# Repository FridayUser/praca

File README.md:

View this project on [CADLAB.io](https://cadlab.io/project/28597). 

# praca

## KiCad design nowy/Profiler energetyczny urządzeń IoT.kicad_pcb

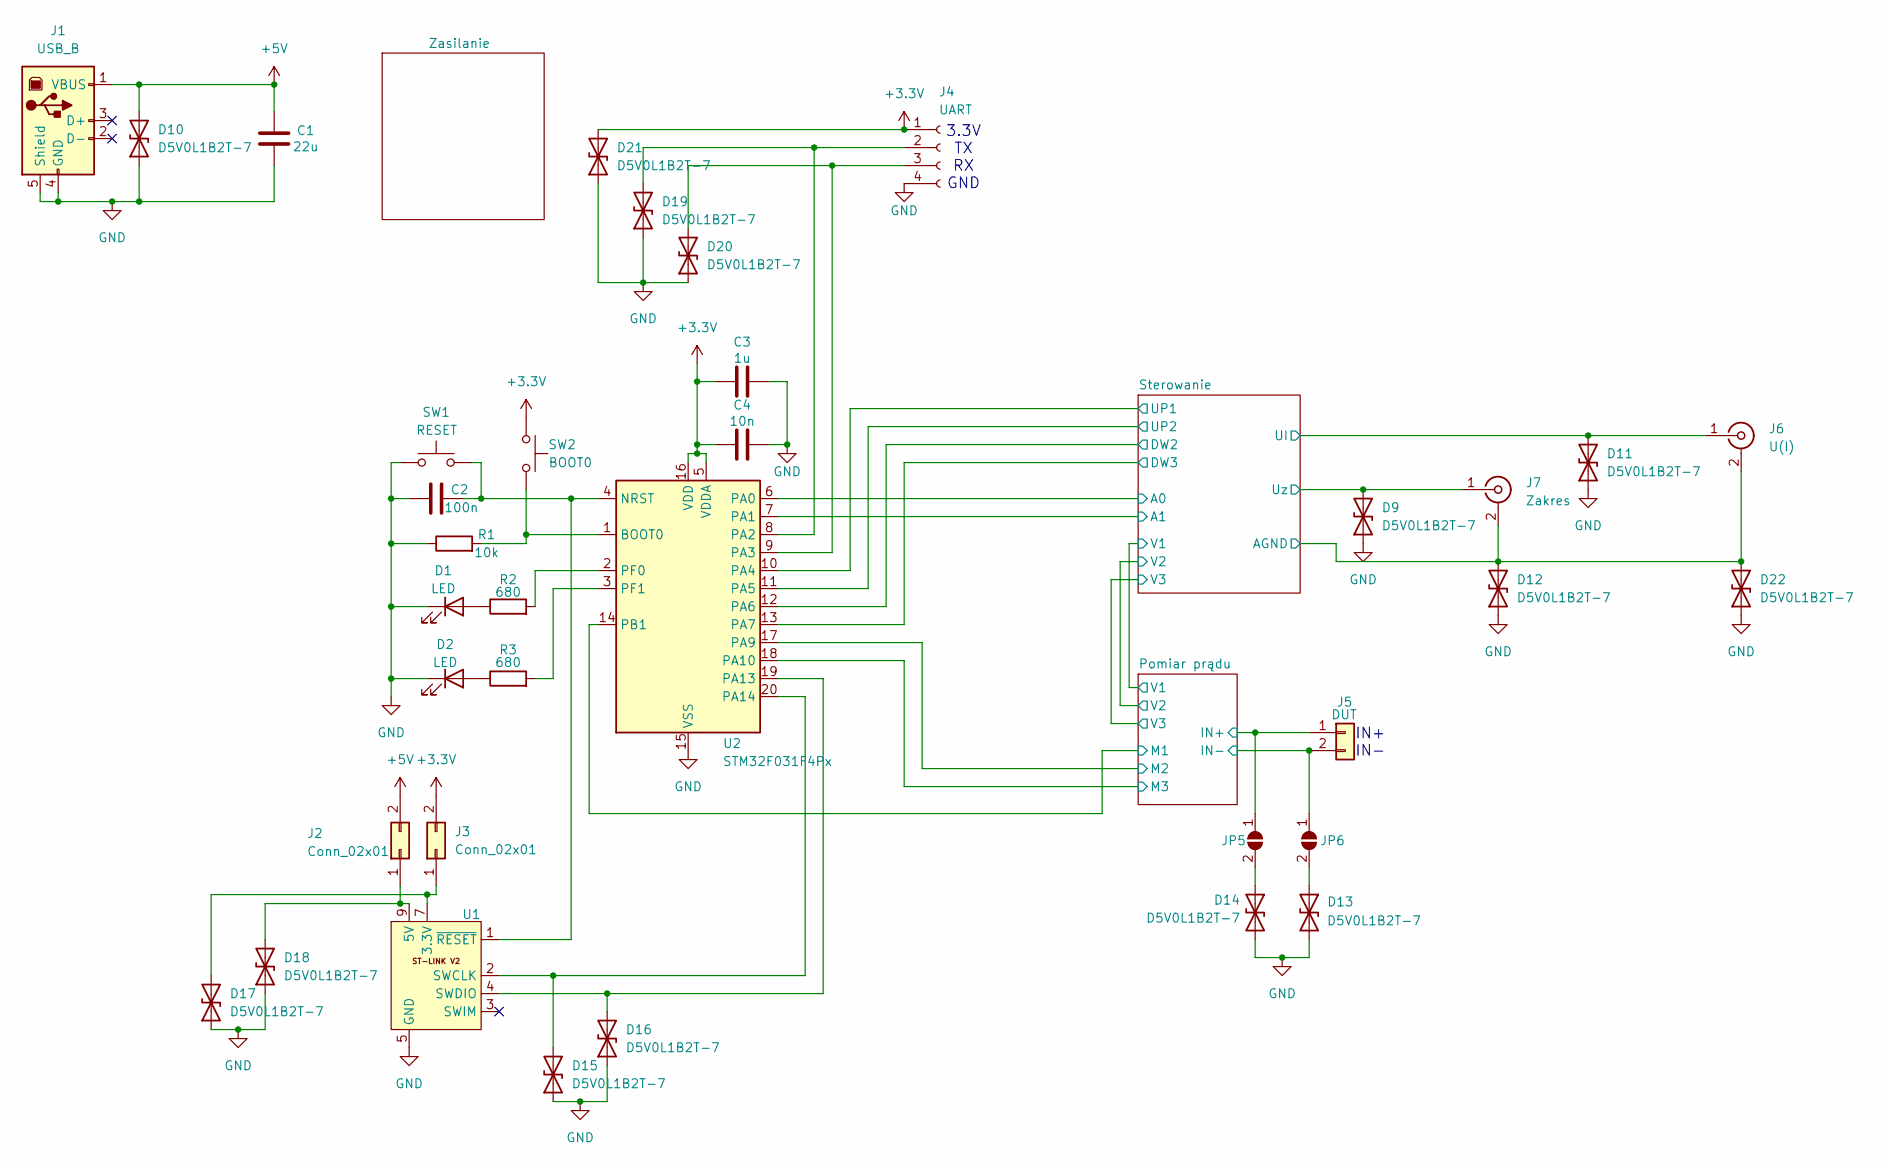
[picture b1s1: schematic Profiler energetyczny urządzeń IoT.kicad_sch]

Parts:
C1: 22u; C_1206_3216Metric_Pad1.33x1.80mm_HandSolder
C2: 100n; C_0805_2012Metric_Pad1.18x1.45mm_HandSolder
C3: 1u; C_0805_2012Metric_Pad1.18x1.45mm_HandSolder
C4: 10n; C_0805_2012Metric_Pad1.18x1.45mm_HandSolder
D1, D2: LED; LED_miniPLCC_2315_Handsoldering
D9, D10, D11, D12, D13, D14, D15, D16, D17, D18, D19, D20, D21, D22: D5V0L1B2T-7; D_SOD-523
J1: USB_B; USB_B_OST_USB-B1HSxx_Horizontal
J2, J3: Conn_02x01; PinHeader_2x01_P2.54mm_Vertical
J4: UART; PinSocket_1x04_P2.54mm_Vertical
J5: DUT; SolderWire-2sqmm_1x02_P7.8mm_D2mm_OD3.9mm
J6: U(I); BNC_Amphenol_B6252HB-NPP3G-50_Horizontal
J7: Zakres; BNC_Amphenol_B6252HB-NPP3G-50_Horizontal
JP5, JP6: SolderJumper_2_Open; SolderJumper-2_P1.3mm_Open_TrianglePad1.0x1.5mm
R1: 10k; R_0805_2012Metric_Pad1.20x1.40mm_HandSolder
R2, R3: 680; R_0805_2012Metric_Pad1.20x1.40mm_HandSolder
SW1: RESET; SW_SPST_TL3305A
SW2: BOOT0; SW_SPST_TL3305A
U1: IDC-Header_2x05_P2.54mm_Vertical
U2: STM32F031F4Px; TSSOP-20_4.4x6.5mm_P0.65mm

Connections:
3.3V: D17.2 (A2), J3.1, U1.7 (3.3V), U1.8 (3.3V)
5V: D18.2 (A2), J2.1, U1.9 (5V), U1.10 (5V)
+3.3V: C3.1, C4.1, D21.2 (A2), J3.2, J4.1, SW2.1, U2.5 (VDDA), U2.16 (VDD); also elsewhere on the board
+5V: C1.1, D10.2 (A2), J1.1 (VBUS), J2.2; also elsewhere on the board
/M3: U2.18 (PA10)
/Pomiar prądu/IN+: J5.1, JP5.1 (A); also elsewhere on the board
/Pomiar prądu/M1: U2.14 (PB1); also elsewhere on the board
/Pomiar prądu/M2: U2.17 (PA9); also elsewhere on the board
/Sterowanie/A0: U2.6 (PA0); also elsewhere on the board
/Sterowanie/A1: U2.7 (PA1); also elsewhere on the board
/Sterowanie/DW2: U2.12 (PA6); also elsewhere on the board
/Sterowanie/DW3: U2.13 (PA7); also elsewhere on the board
/Sterowanie/UI: D11.2 (A2), J6.1 (In); also elsewhere on the board
/Sterowanie/UP1: U2.10 (PA4); also elsewhere on the board
/Sterowanie/UP2: U2.11 (PA5); also elsewhere on the board
/Sterowanie/Uz: D9.2 (A2), J7.1 (In); also elsewhere on the board
GND: C1.2, C2.1, C3.2, C4.2, D1.1 (K), D2.1 (K), D9.1 (A1), D10.1 (A1), D11.1 (A1), D12.1 (A1), D12.2 (A2), D13.2 (A2), D14.2 (A2), D15.1 (A1), D16.1 (A1), D17.1 (A1), D18.1 (A1), D19.1 (A1), D20.1 (A1), D21.1 (A1), D22.1 (A1), D22.2 (A2), J1.4 (GND), J1.5 (Shield), J4.4, J5.2, J6.2 (Ext), J7.2 (Ext), JP6.1 (A), R1.1, SW1.1, U1.5 (GND), U1.6 (GND), U2.15 (VSS); also elsewhere on the board
unnamed: D1.2 (A), R2.1
unnamed: D2.2 (A), R3.1
unnamed: D13.1 (A1), JP6.2 (B)
unnamed: D14.1 (A1), JP5.2 (B)
unnamed: D15.2 (A2), U1.2 (SWCLK), U2.20 (PA14)
unnamed: D16.2 (A2), U1.4 (SWDIO), U2.19 (PA13)
unnamed: D19.2 (A2), J4.2, U2.8 (PA2)
unnamed: D20.2 (A2), J4.3, U2.9 (PA3)
unnamed: C2.2, SW1.2, U1.1 (~RESET), U2.4 (NRST)
unnamed: R1.2, SW2.2, U2.1 (BOOT0)
unnamed: R2.2, U2.2 (PF0)
unnamed: R3.2, U2.3 (PF1)

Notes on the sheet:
IN+ IN-
3.3V TX RX GND

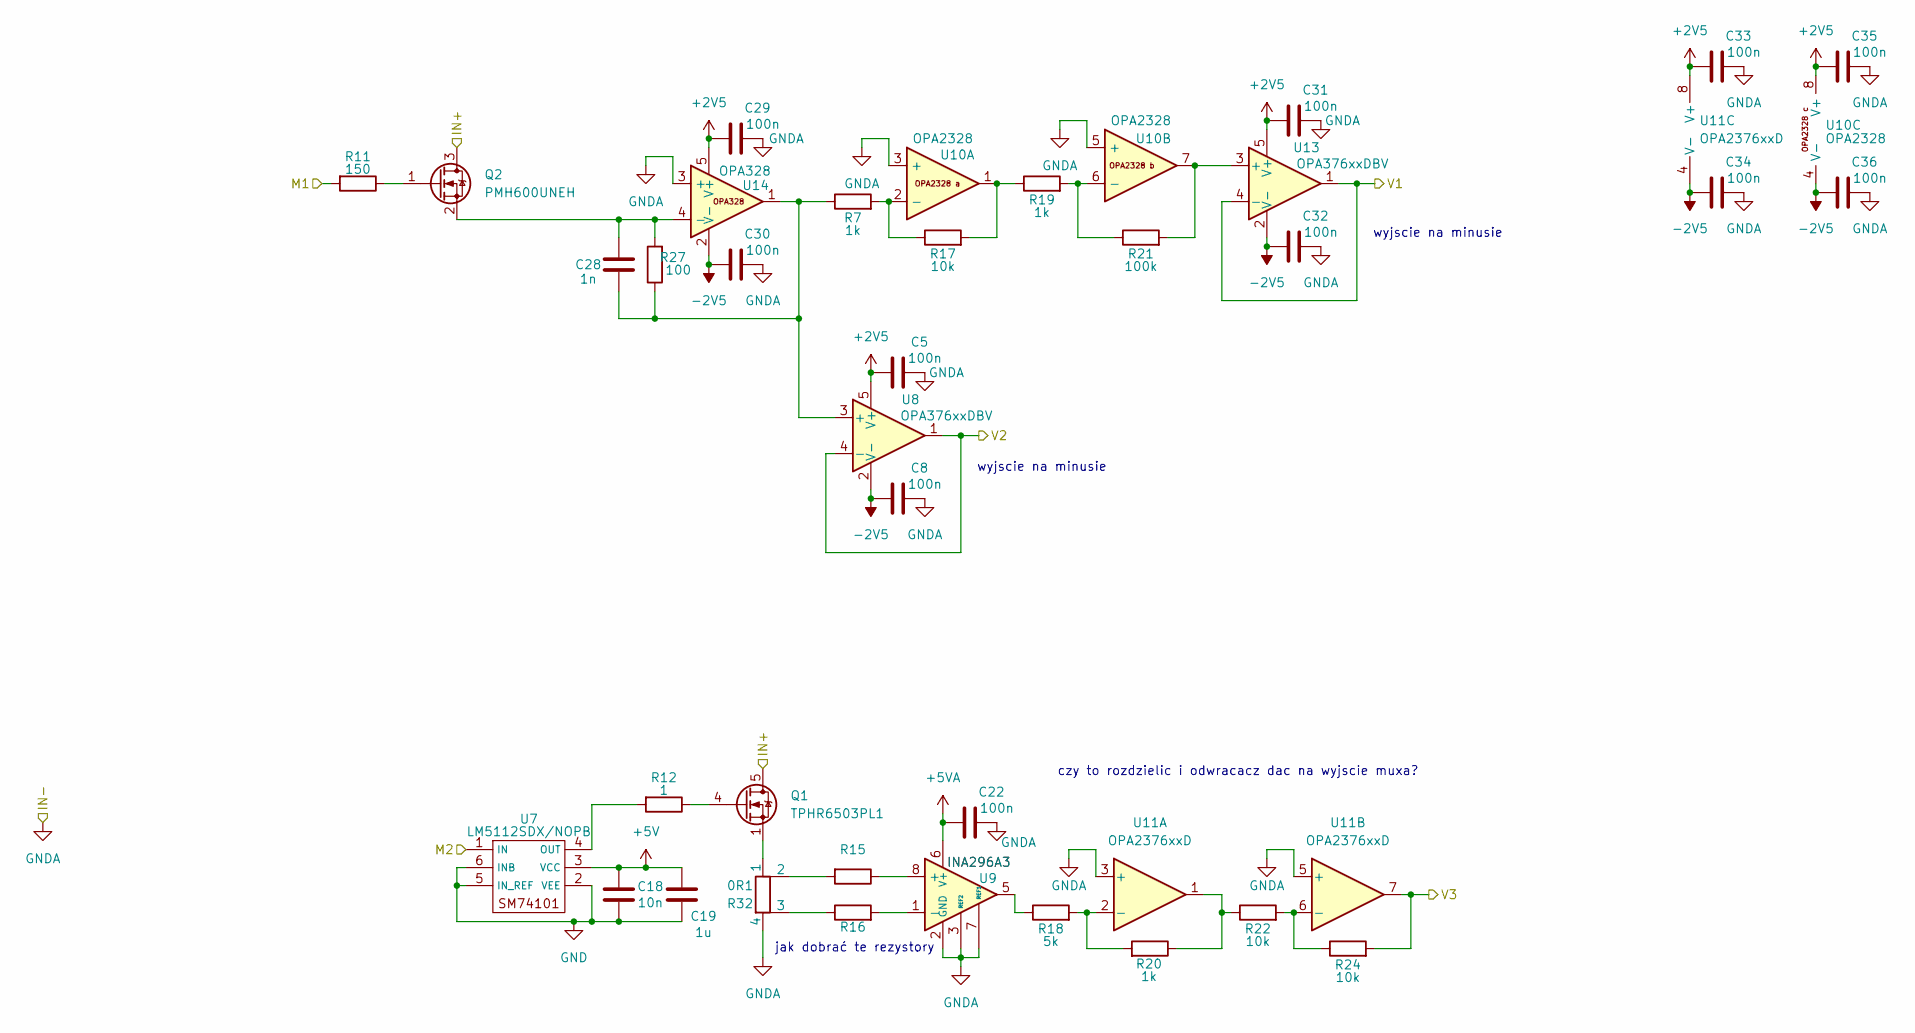
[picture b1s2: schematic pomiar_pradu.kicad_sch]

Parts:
C5, C8, C22, C29, C30, C31, C32, C33, C34, C35, C36: 100n; C_0805_2012Metric_Pad1.18x1.45mm_HandSolder
C18: 10n; C_0805_2012Metric_Pad1.18x1.45mm_HandSolder
C19: 1u; C_0805_2012Metric_Pad1.18x1.45mm_HandSolder
C28: 1n; C_0805_2012Metric_Pad1.18x1.45mm_HandSolder
Q1: TPHR6503PL1; TDSON-8-1
Q2: PMH600UNEH; DFN606-3
R7, R19, R20: 1k; R_0805_2012Metric_Pad1.20x1.40mm_HandSolder
R11: 150; R_0805_2012Metric_Pad1.20x1.40mm_HandSolder
R12: 1; R_0805_2012Metric_Pad1.20x1.40mm_HandSolder
R15, R16: R_0805_2012Metric_Pad1.20x1.40mm_HandSolder
R17, R22, R24: 10k; R_0805_2012Metric_Pad1.20x1.40mm_HandSolder
R18: 5k; R_0805_2012Metric_Pad1.20x1.40mm_HandSolder
R21: 100k; R_0805_2012Metric_Pad1.20x1.40mm_HandSolder
R27: 100; R_0805_2012Metric_Pad1.20x1.40mm_HandSolder
R32: 0R1; R_Shunt_Ohmite_LVK12
U7: LM5112SDX/NOPB; WSON
U8, U13: OPA376xxDBV; SOT-23-5
U9: INA296A3; SOIC-8_3.9x4.9mm_P1.27mm
U10: OPA2328; VSSOP-8_3.0x3.0mm_P0.65mm
U11: OPA2376xxD; SOIC-8_3.9x4.9mm_P1.27mm
U14: OPA328; SOT-23-5_HandSoldering

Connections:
+2V5: C5.1, C29.1, C31.1, C33.1, C35.1, U8.5 (V+), U10.8 (V+), U11.8 (V+), U13.5 (V+), U14.5 (V+); also elsewhere on the board
+5V: C18.1, C19.1, U7.3 (VCC); also elsewhere on the board
+5VA: C22.1, U9.6 (V+); also elsewhere on the board
-2V5: C8.1, C30.1, C32.1, C34.1, C36.1, U8.2 (V-), U10.4 (V-), U11.4 (V-), U13.2 (V-), U14.2 (V-); also elsewhere on the board
/Pomiar prądu/IN+: Q1.5 (D), Q2.3 (D); also elsewhere on the board
/Pomiar prądu/M1: R11.2; also elsewhere on the board
/Pomiar prądu/M2: U7.1 (IN); also elsewhere on the board
/Pomiar prądu/V1: U13.1, U13.4 (-); also elsewhere on the board
/Pomiar prądu/V2: U8.1, U8.4 (-); also elsewhere on the board
/Pomiar prądu/V3: R24.2, U11.7; also elsewhere on the board
GND: C5.2, C8.2, C18.2, C19.2, C22.2, C29.2, C30.2, C31.2, C32.2, C33.2, C34.2, C35.2, C36.2, R32.4, U7.2 (VEE), U7.5 (IN_REF), U7.6 (INB), U9.2 (GND), U9.3 (REF2), U9.4 (GND), U9.7 (REF1), U10.3 (+), U10.5 (+), U11.3 (+), U11.5 (+), U14.3 (+); also elsewhere on the board
unnamed: Q1.4 (G), R12.1
unnamed: Q1.1 (S), Q1.2 (S), Q1.3 (S), R32.1
unnamed: Q2.1 (G), R11.1
unnamed: C28.2, Q2.2 (S), R27.2, U14.4 (-)
unnamed: R15.2, R32.2
unnamed: R16.1, R32.3
unnamed: R17.2, R19.1, U10.1
unnamed: R18.1, U9.5
unnamed: R20.1, R22.1, U11.1
unnamed: R12.2, U7.4 (OUT)
unnamed: C28.1, R7.1, R27.1, U8.3 (+), U14.1
unnamed: R15.1, U9.8 (+)
unnamed: R16.2, U9.1 (-)
unnamed: R7.2, R17.1, U10.2 (-)
unnamed: R19.2, R21.1, U10.6 (-)
unnamed: R18.2, R20.2, U11.2 (-)
unnamed: R22.2, R24.1, U11.6 (-)
unnamed: R21.2, U10.7, U13.3 (+)

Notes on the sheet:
czy to rozdzielic i odwracacz dac na wyjscie muxa?
jak dobrać te rezystory
wyjscie na minusie

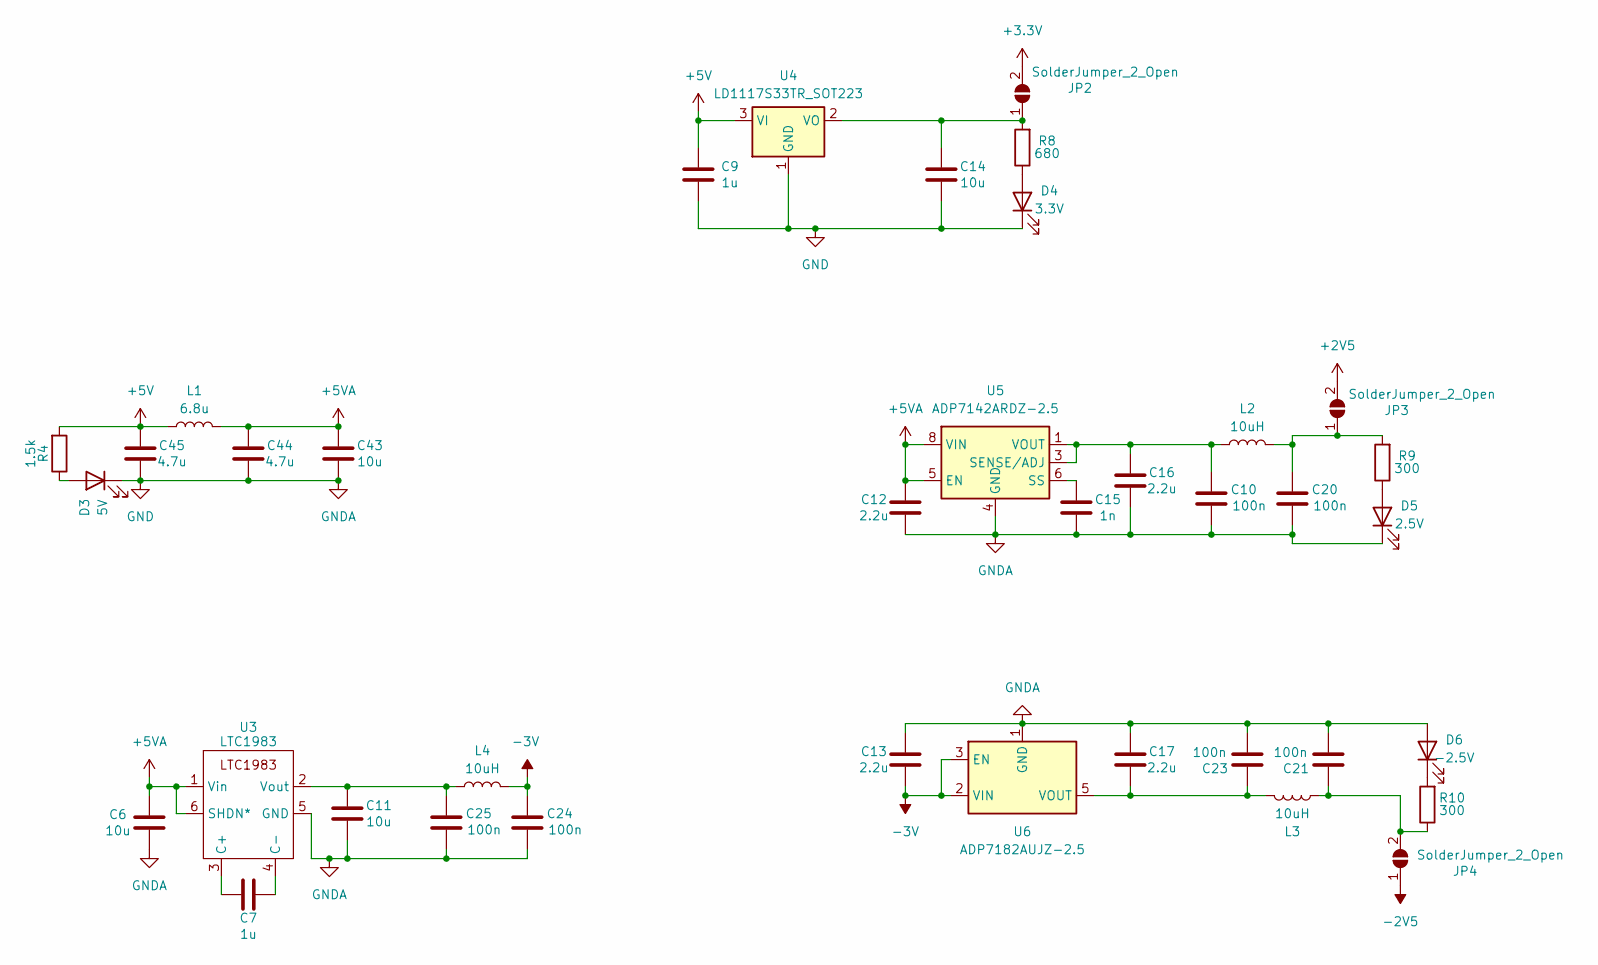
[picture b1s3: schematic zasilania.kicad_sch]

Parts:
C6, C11, C14, C43: 10u; C_0805_2012Metric_Pad1.18x1.45mm_HandSolder
C7, C9: 1u; C_0805_2012Metric_Pad1.18x1.45mm_HandSolder
C10, C20, C21, C23, C24, C25: 100n; C_0805_2012Metric_Pad1.18x1.45mm_HandSolder
C12, C13, C16, C17: 2.2u; C_0805_2012Metric_Pad1.18x1.45mm_HandSolder
C15: 1n; C_0805_2012Metric_Pad1.18x1.45mm_HandSolder
C44, C45: 4.7u; C_0805_2012Metric_Pad1.18x1.45mm_HandSolder
D3: 5V; LED_miniPLCC_2315_Handsoldering
D4: 3.3V; LED_miniPLCC_2315_Handsoldering
D5: 2.5V; LED_miniPLCC_2315_Handsoldering
D6: -2.5V; LED_miniPLCC_2315_Handsoldering
JP2, JP3, JP4: SolderJumper_2_Open; SolderJumper-2_P1.3mm_Open_TrianglePad1.0x1.5mm
L1: 6.8u; L_Wuerth_WE-PD2-Typ-MS
L2, L3, L4: 10uH; L_1210_3225Metric_Pad1.42x2.65mm_HandSolder
R4: 1.5k; R_0805_2012Metric_Pad1.20x1.40mm_HandSolder
R8: 680; R_0805_2012Metric_Pad1.20x1.40mm_HandSolder
R9, R10: 300; R_0805_2012Metric_Pad1.20x1.40mm_HandSolder
U3: LTC1983; SOT-23-6_Handsoldering
U4: LD1117S33TR_SOT223; SOT-223-3_TabPin2
U5: ADP7142ARDZ-2.5; SOIC-8-1EP_3.9x4.9mm_P1.27mm_EP2.29x3mm
U6: ADP7182AUJZ-2.5; TSOT-23-5

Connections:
+2V5: JP3.2 (B); also elsewhere on the board
+3.3V: JP2.2 (B); also elsewhere on the board
+5V: C9.1, C45.1, L1.1, R4.2, U4.3 (VI); also elsewhere on the board
+5VA: C6.1, C12.1, C43.1, C44.1, L1.2, U3.1 (Vin), U3.6 (SHDN*), U5.5 (EN), U5.7 (VIN), U5.8 (VIN); also elsewhere on the board
-2V5: JP4.1 (A); also elsewhere on the board
-3V: C13.2, C24.2, L4.2, U6.2 (VIN), U6.3 (EN)
GND: C6.2, C9.2, C10.1, C11.2, C12.2, C13.1, C14.2, C15.2, C16.2, C17.1, C20.1, C21.1, C23.1, C24.1, C25.1, C43.2, C44.2, C45.2, D3.1 (K), D4.1 (K), D5.1 (K), D6.2 (A), U3.5 (GND), U4.1 (GND), U5.4 (GND), U5.9 (GND), U6.1 (GND); also elsewhere on the board
unnamed: D3.2 (A), R4.1
unnamed: D4.2 (A), R8.1
unnamed: D5.2 (A), R9.1
unnamed: D6.1 (K), R10.2
unnamed: C14.1, JP2.1 (A), R8.2, U4.2 (VO)
unnamed: C20.2, JP3.1 (A), L2.2, R9.2
unnamed: C21.2, JP4.2 (B), L3.1, R10.1
unnamed: C7.2, U3.3 (C+)
unnamed: C7.1, U3.4 (C-)
unnamed: C11.1, C25.2, L4.1, U3.2 (Vout)
unnamed: C10.2, C16.1, L2.1, U5.1 (VOUT), U5.2 (VOUT), U5.3 (SENSE/ADJ)
unnamed: C15.1, U5.6 (SS)
unnamed: C17.2, C23.2, L3.2, U6.5 (VOUT)

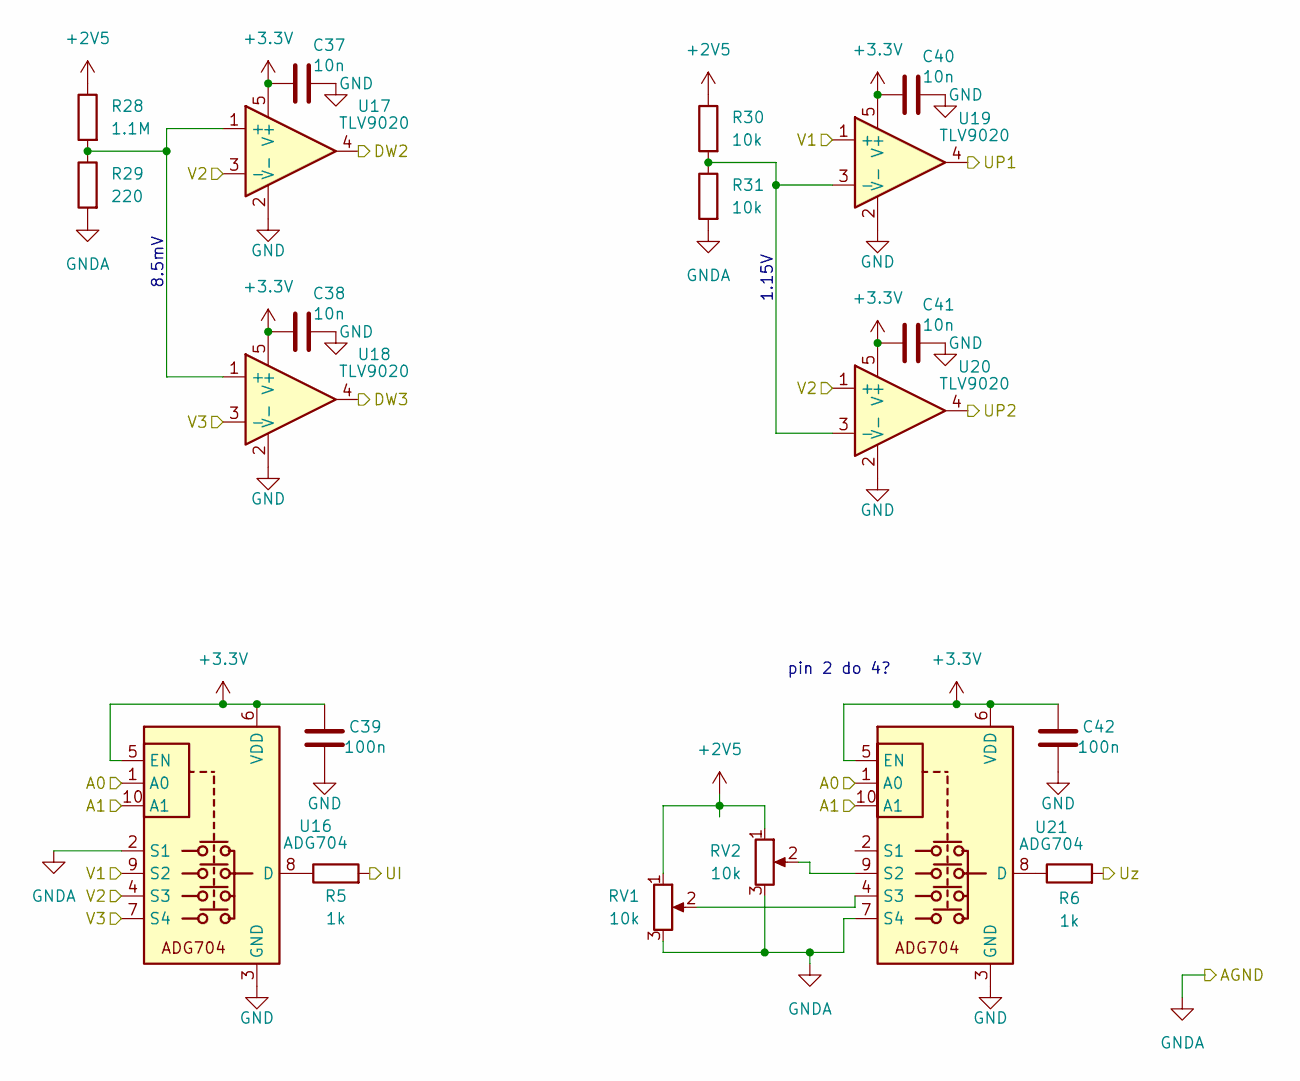
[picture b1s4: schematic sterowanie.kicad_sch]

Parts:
C37, C38, C40, C41: 10n; C_0805_2012Metric_Pad1.18x1.45mm_HandSolder
C39, C42: 100n; C_0805_2012Metric_Pad1.18x1.45mm_HandSolder
R5, R6: 1k; R_0805_2012Metric_Pad1.20x1.40mm_HandSolder
R28: 1.1M; R_0805_2012Metric_Pad1.20x1.40mm_HandSolder
R29: 220; R_0805_2012Metric_Pad1.20x1.40mm_HandSolder
R30, R31: 10k; R_0805_2012Metric_Pad1.20x1.40mm_HandSolder
RV1, RV2: 10k; Potentiometer_Bourns_3266W_Vertical
U16, U21: ADG704; MSOP-10_3x3mm_P0.5mm
U17, U18, U19, U20: TLV9020; SOT-23-5_HandSoldering

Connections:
+2V5: R28.1, R30.1, RV1.1, RV2.1; also elsewhere on the board
+3.3V: C37.1, C38.1, C39.1, C40.1, C41.1, C42.1, U16.5 (EN), U16.6 (VDD), U17.5 (V+), U18.5 (V+), U19.5 (V+), U20.5 (V+), U21.5 (EN), U21.6 (VDD); also elsewhere on the board
/Pomiar prądu/V1: U16.9 (S2), U19.1 (+); also elsewhere on the board
/Pomiar prądu/V2: U16.4 (S3), U17.3 (-), U20.1 (+); also elsewhere on the board
/Pomiar prądu/V3: U16.7 (S4), U18.3 (-); also elsewhere on the board
/Sterowanie/A0: U16.1 (A0), U21.1 (A0); also elsewhere on the board
/Sterowanie/A1: U16.10 (A1), U21.10 (A1); also elsewhere on the board
/Sterowanie/DW2: U17.4; also elsewhere on the board
/Sterowanie/DW3: U18.4; also elsewhere on the board
/Sterowanie/UI: R5.2; also elsewhere on the board
/Sterowanie/UP1: U19.4; also elsewhere on the board
/Sterowanie/UP2: U20.4; also elsewhere on the board
/Sterowanie/Uz: R6.2; also elsewhere on the board
GND: C37.2, C38.2, C39.2, C40.2, C41.2, C42.2, R29.2, R31.2, RV1.3, RV2.3, U16.2 (S1), U16.3 (GND), U17.2 (V-), U18.2 (V-), U19.2 (V-), U20.2 (V-), U21.3 (GND), U21.7 (S4); also elsewhere on the board
unnamed: R5.1, U16.8 (D)
unnamed: R28.2, R29.1, U17.1 (+), U18.1 (+)
unnamed: R30.2, R31.1, U19.3 (-), U20.3 (-)
unnamed: R6.1, U21.8 (D)
unnamed: RV2.2, U21.9 (S2)
unnamed: RV1.2, U21.4 (S3)

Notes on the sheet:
8.5mV
1.15V
pin 2 do 4?

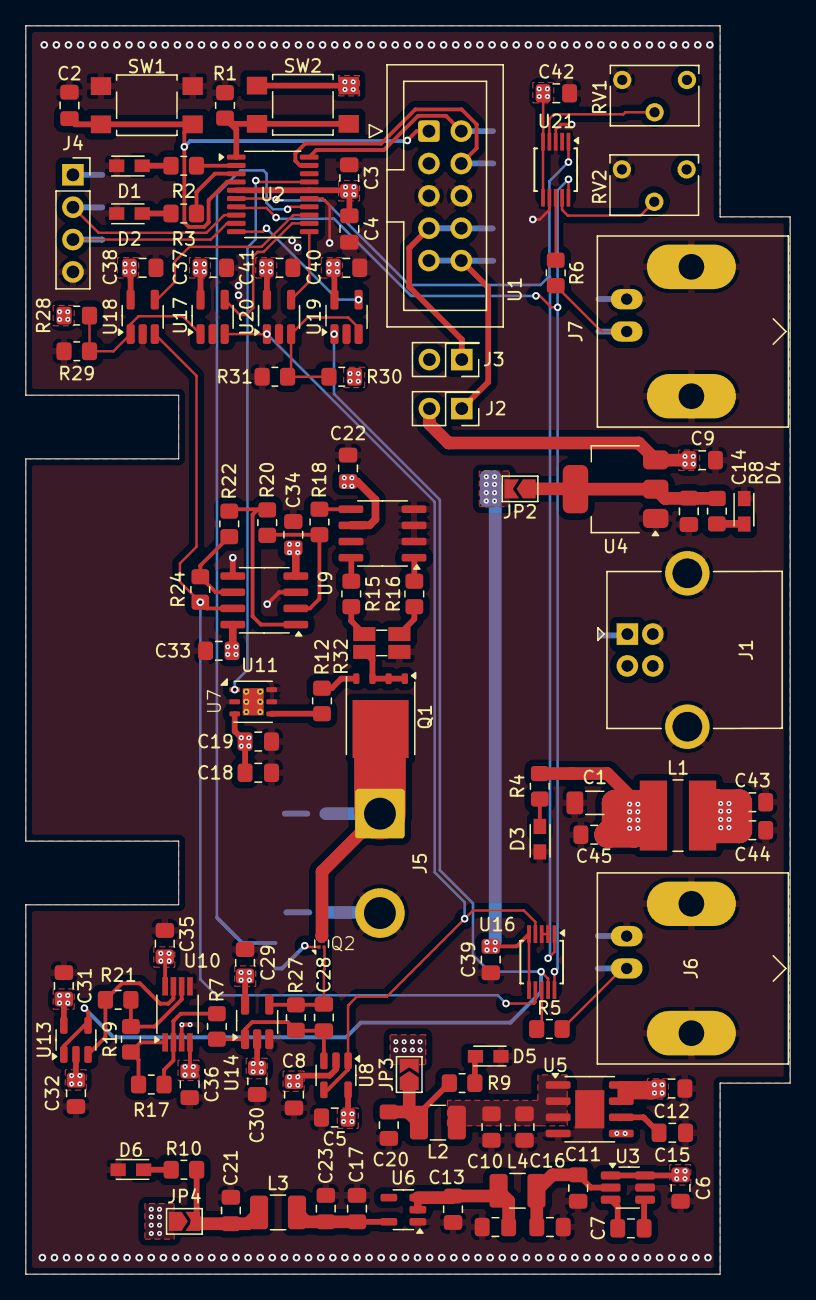
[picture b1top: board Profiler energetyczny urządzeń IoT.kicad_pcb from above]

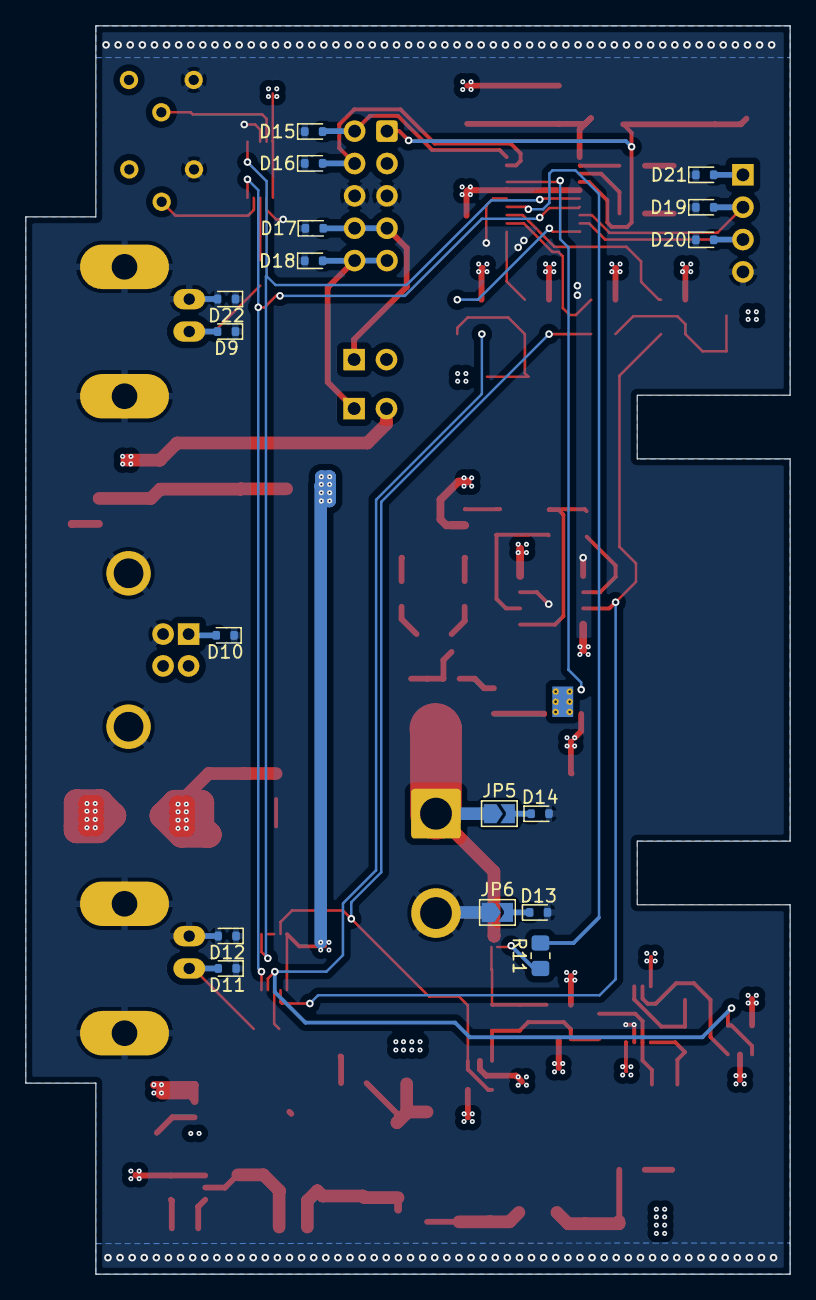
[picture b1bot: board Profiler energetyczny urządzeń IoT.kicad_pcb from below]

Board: 4 copper layers, 60.0 x 98.0 mm, 131 parts (17 on the bottom side), 72 nets.

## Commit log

2024-10-24 Backlink to CADLAB.io has been added.
